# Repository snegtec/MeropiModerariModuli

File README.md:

/*****************************************************************************
*
* MEROPI MODERARI MODULI
* a simple microcontroller system for controlling light output of linear 
* fluorescent tube according to saved program
* 
* version: 0.3 (November 2020)
* author: Erik Kos
*   snegtec.com
*   snegtec@outlook.com
* 
* Copyright (c) 2014-2020 Erik Kos
* License:
*   application, source code - GNU General Public License
*   hardware (schematics, pcb design) - Creative Commons Attribution 
*   Share-Alike license (CC BY-SA 4.0)
* 
****************************************************************************/

Used tools
* compiler: Atmel Studio 6
* application for pcb design: Eagle 6.5.0.

Notes
* this is a beta version!
* pcb for power and relay modules are one-sided; you can create it cheaper than 2 sided versions.

Important note!
* The power module use 230V. There could requirements in your country about design and electrical rules for design of such devices. If you are not confident when working with such voltages don't use the power module. Use ready power supply. 

TODO
* it is better to use external oscilator
* it would be good idea to add socket for serial (txd, rxd); for example during reset Bluetooth connection is lost; it is not a problem in final, production environment but during debug it bothers;
* holes for mounting the boards could have bigger diameter
* cloud events hasn't been tested too carefully; only PWM1 pin has support for cloud events
* no support for daylight saving time 
* add more meaningful captions for elements on pcb boards; like 5V or 3,3V instead of X5 or X3;

Bugs
* There is support for bigger buffer for transmission of AT commands. But sometimes there is a problem that the end of the line disapears when parsed.

Bootloader information
* My version of module uses ATMEL AVR UART Bootloader for AVR-GCC/avr-libc. It is not needed for modules to work. But it can be very helpful to update software when a final module is mounted in a place where there is difficult access.

* MMM software has support for butterfly compatible programmer. It allows for touchless programming of the module. No need to press any button before programming the device. Programmer needs just to use Bluetooth serial port. You start programming, the module resets and bootloader loads into memory and loads new program to memory. More info in utils_com.c file on line 536.

More information about bootloader:
* ATMEL AVR UART Bootloader for AVR-GCC/avr-libc
* by Martin Thomas, Kaiserslautern, Germany
* mthomas@rhrk.uni-kl.de
* eversmith@heizung-thomas.de
* http://www.siwawi.arubi.uni-kl.de/avr_projects

/****************************************************************************/

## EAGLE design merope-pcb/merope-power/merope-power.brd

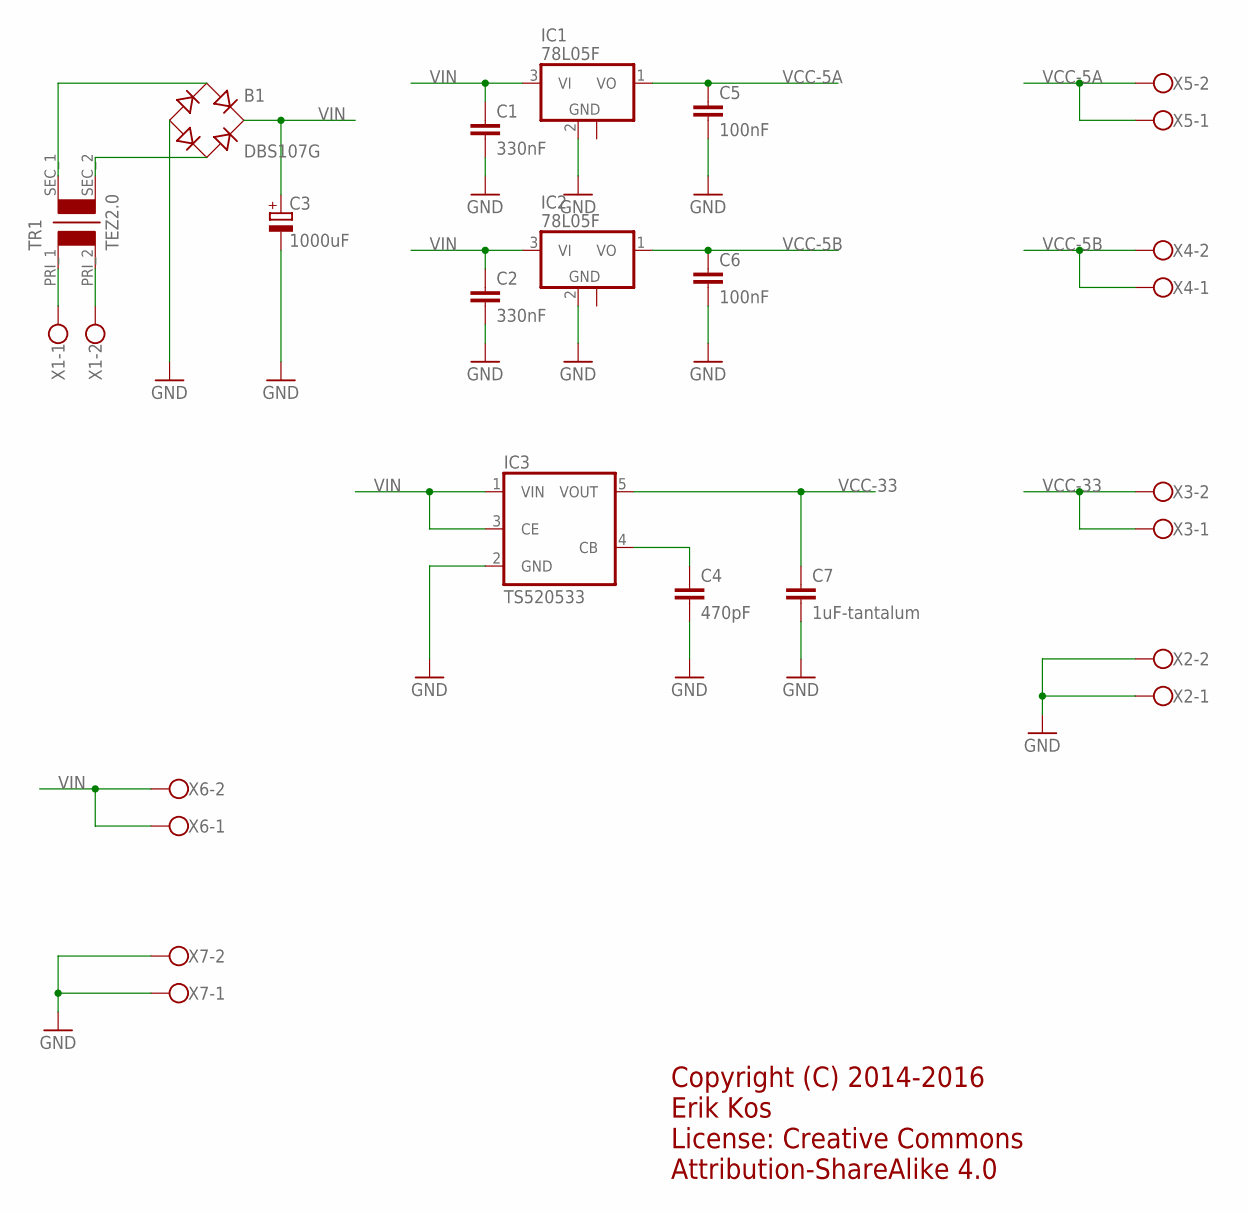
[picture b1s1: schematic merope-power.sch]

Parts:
B1: DBS107G; DBS
C1, C2: 330nF; C0805
C3: 1000uF; TT5D11
C4: 470pF; C0805
C5, C6: 100nF; C0805
C7: 1uF-tantalum; C0805
IC1, IC2: 78L05F; SOT89
IC3: TS520533; SOT25
TR1: TEZ2.0
X1: TERMINAL_BLOCK_5_2
X2, X3, X4, X5, X6, X7: TERMINAL_BLOCK_35_2

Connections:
GND: B1.-, C1.2, C2.2, C3.-, C4.2, C5.2, C6.2, C7.2, IC1.2 (GND), IC2.2 (GND), IC3.2 (GND), X2.1, X2.2, X7.1, X7.2
unnamed: B1.AC1, TR1.SEC_1
unnamed: C4.1, IC3.4 (CB)
unnamed: B1.AC2, TR1.SEC_2
unnamed: TR1.PRI_1, X1.1
unnamed: TR1.PRI_2, X1.2
VCC-5A: C5.1, IC1.1 (VO), X5.1, X5.2
VCC-5B: C6.1, IC2.1 (VO), X4.1, X4.2
VCC-33: C7.1, IC3.5 (VOUT), X3.1, X3.2
VIN: B1.+, C1.1, C2.1, C3.+, IC1.3 (VI), IC2.3 (VI), IC3.1 (VIN), IC3.3 (CE), X6.1, X6.2

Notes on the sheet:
Copyright (C) 2014-2016 Erik Kos License: Creative Commons Attribution-ShareAlike 4.0

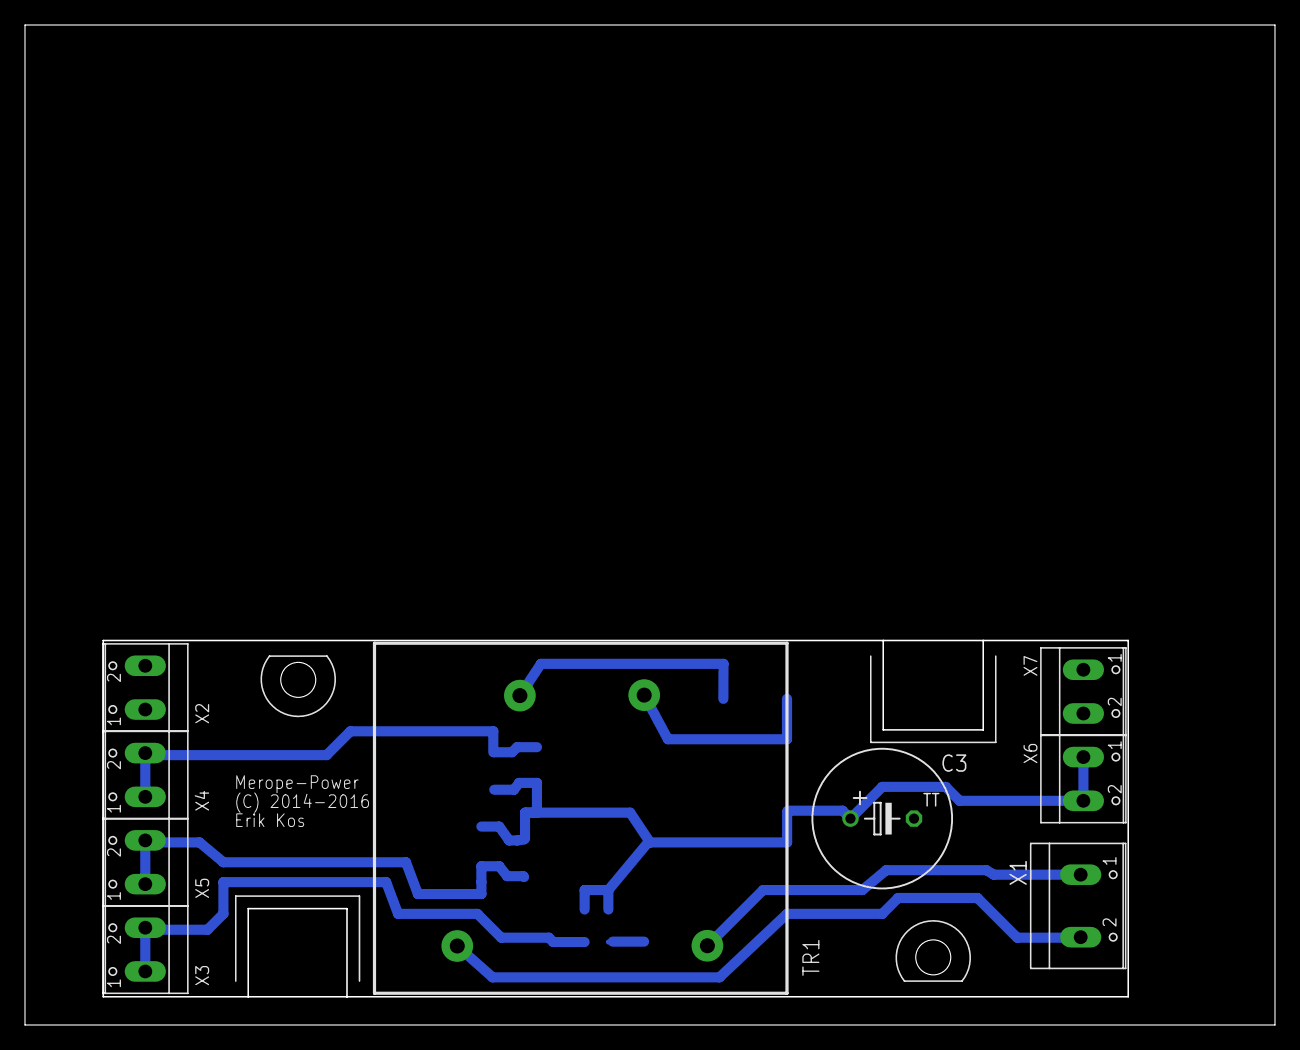
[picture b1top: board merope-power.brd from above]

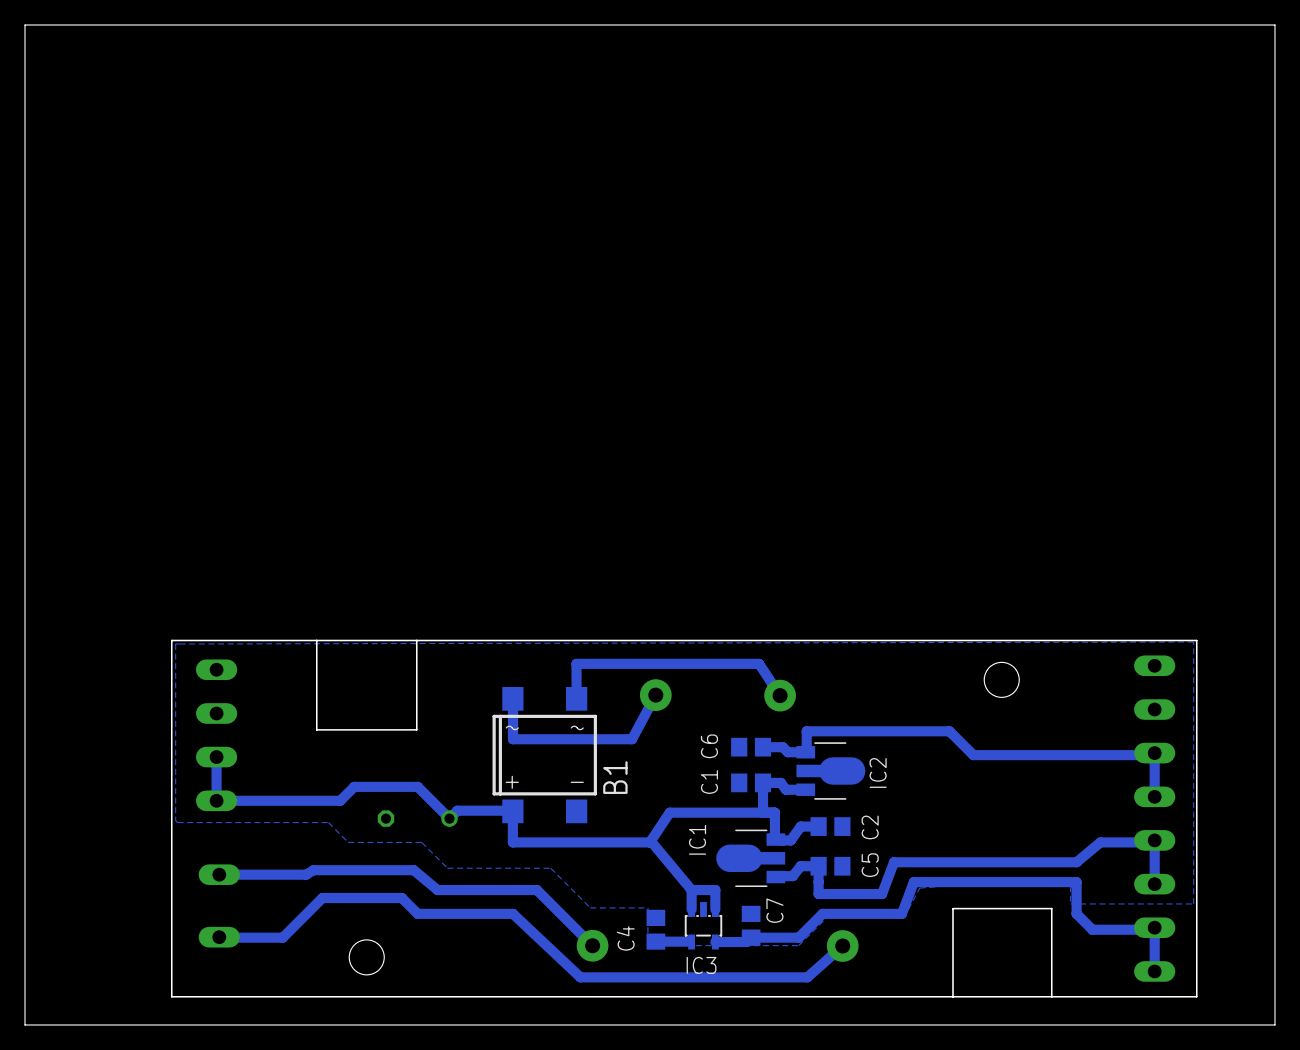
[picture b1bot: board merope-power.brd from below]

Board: 2 copper layers, 100.0 x 80.0 mm, 20 parts (10 on the bottom side), 10 nets.

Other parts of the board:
U$1: Z-103

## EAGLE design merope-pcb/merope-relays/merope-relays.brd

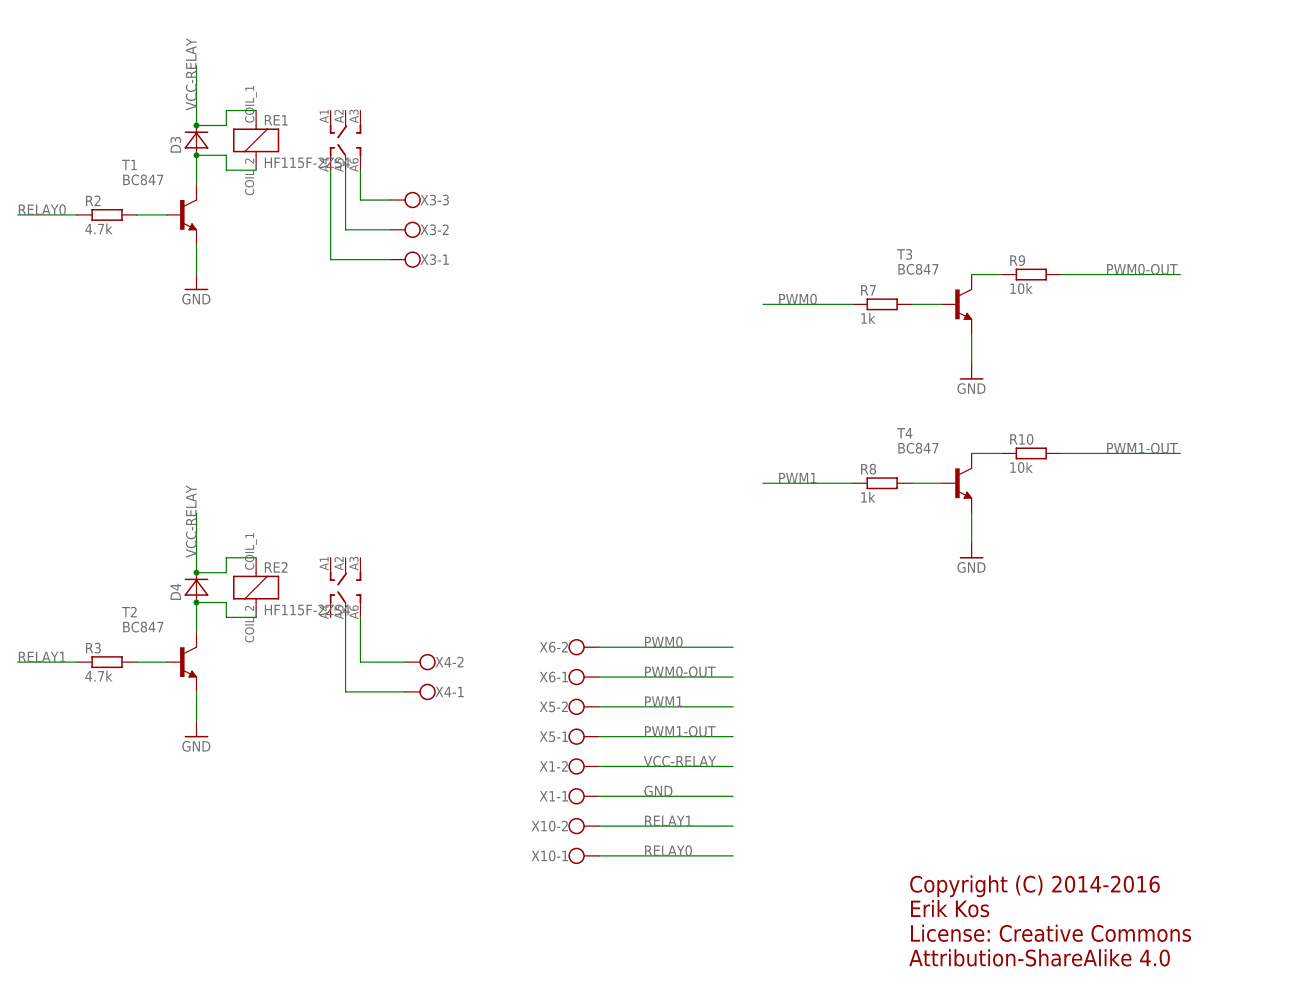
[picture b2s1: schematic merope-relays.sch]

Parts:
D3, D4: DIODE_0805; R0805
R2, R3: 4.7k; M0805
R7, R8: 1k; M0805
R9, R10: 10k; M0805
RE1, RE2: HF115F-2ZS4; HF115F
T1, T2, T3, T4: BC847; SOT23-BEC
X1, X5, X6, X10: TERMINAL_BLOCK_35_2
X3: TERMINAL_BLOCK_5_3
X4: TERMINAL_BLOCK_5_2

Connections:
GND: T1.E, T2.E, T3.E, T4.E, X1.1
unnamed: RE2.A6, X4.2
unnamed: R2.2, T1.B
unnamed: RE1.A6, X3.3
unnamed: RE1.A5, X3.2
unnamed: D3.1 (A), RE1.COIL_2, T1.C
unnamed: RE2.A5, X4.1
unnamed: RE1.A4, X3.1
unnamed: R3.2, T2.B
unnamed: D4.1 (A), RE2.COIL_2, T2.C
unnamed: R7.2, T3.B
unnamed: R9.1, T3.C
unnamed: R8.2, T4.B
unnamed: R10.1, T4.C
PWM0: R7.1, X6.2
PWM0-OUT: R9.2, X6.1
PWM1: R8.1, X5.2
PWM1-OUT: R10.2, X5.1
RELAY0: R2.1, X10.1
RELAY1: R3.1, X10.2
VCC-RELAY: D3.2 (C), D4.2 (C), RE1.COIL_1, RE2.COIL_1, X1.2

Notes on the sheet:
Copyright (C) 2014-2016 Erik Kos License: Creative Commons Attribution-ShareAlike 4.0

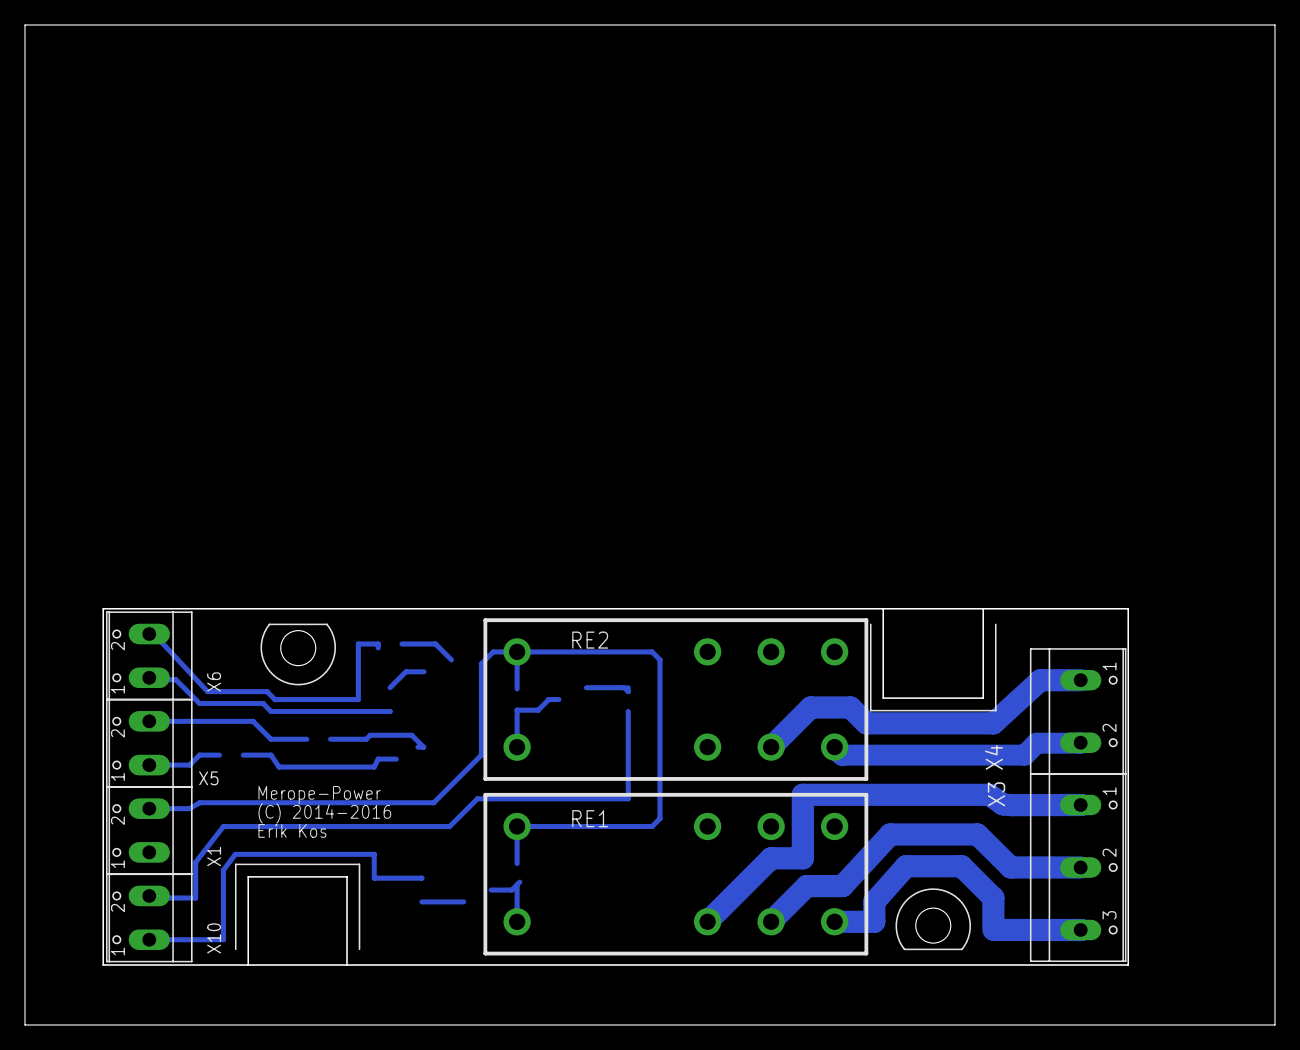
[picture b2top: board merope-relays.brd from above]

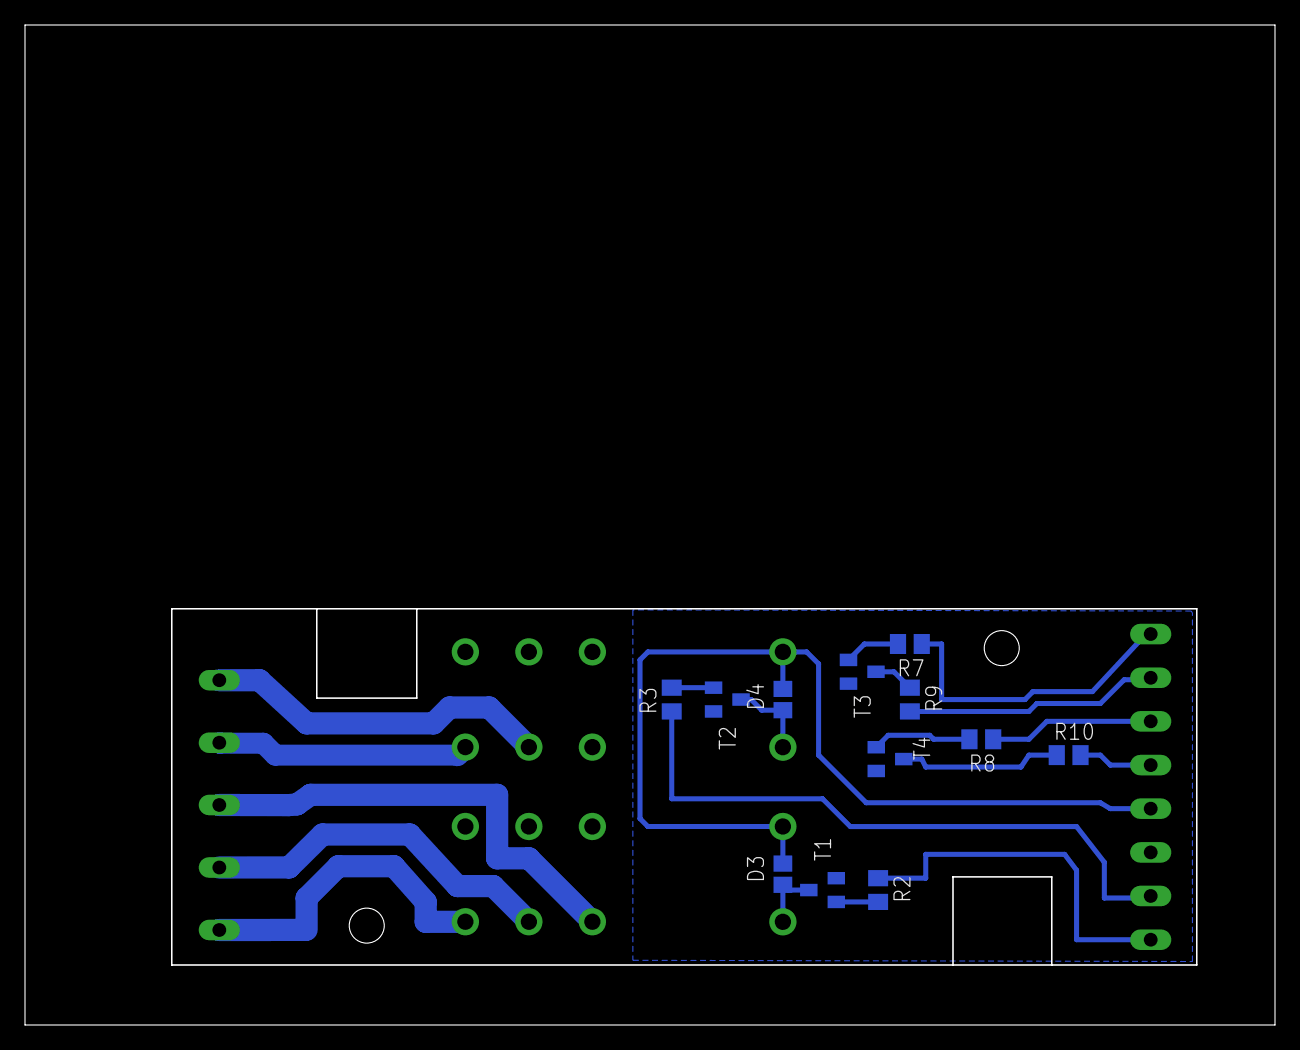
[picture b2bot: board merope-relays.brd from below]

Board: 2 copper layers, 100.0 x 80.0 mm, 21 parts (12 on the bottom side), 21 nets.

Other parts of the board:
U$1: Z-103

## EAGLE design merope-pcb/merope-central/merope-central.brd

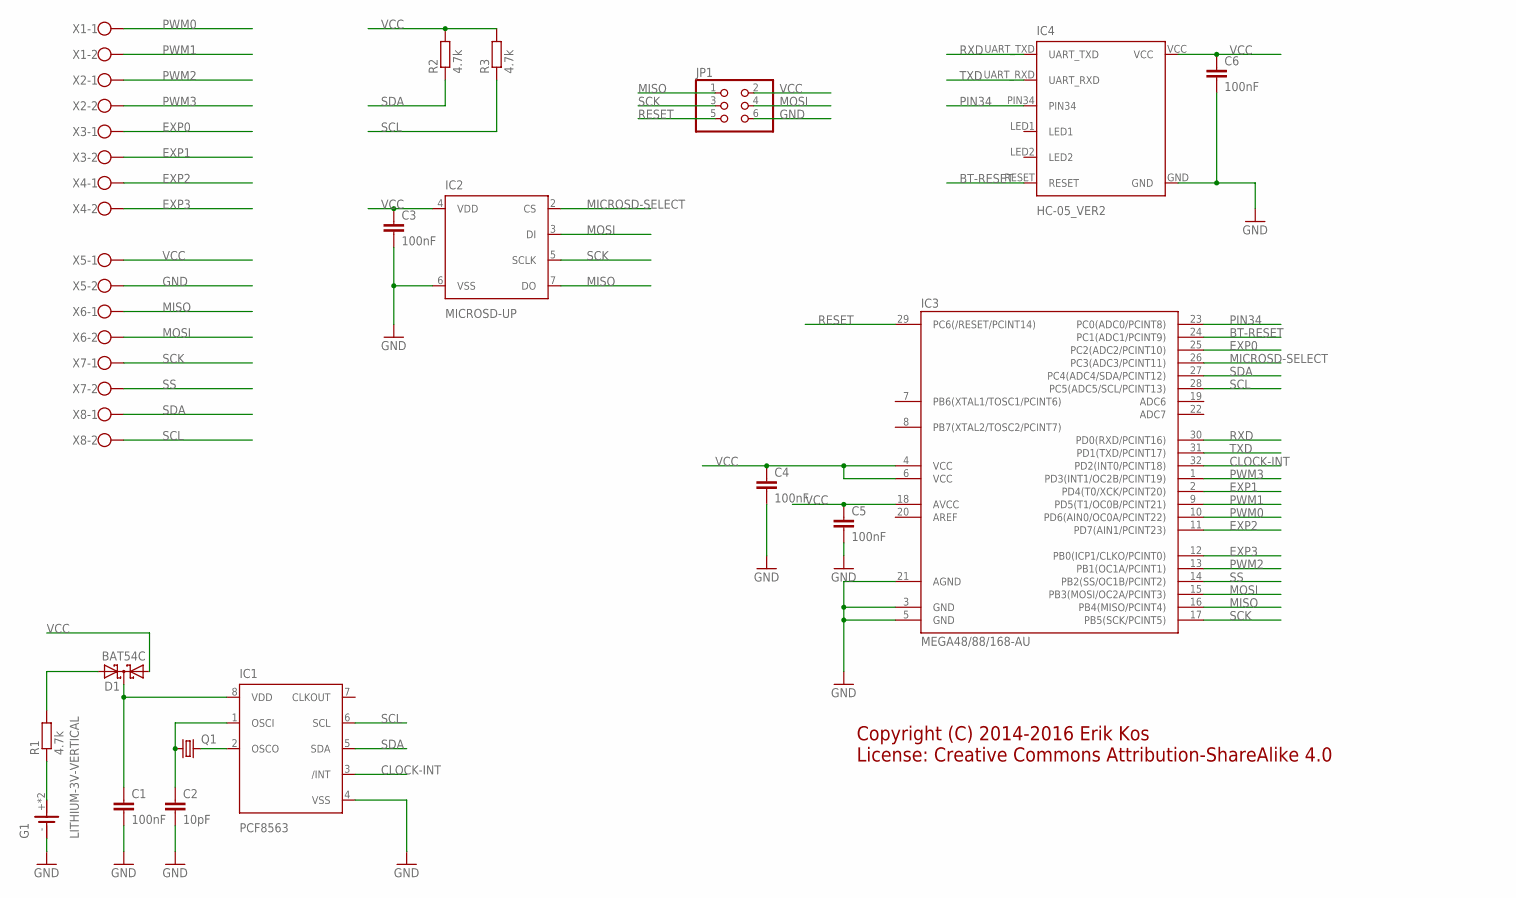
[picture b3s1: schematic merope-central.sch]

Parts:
C1, C3, C4, C5, C6: 100nF; C0805
C2: 10pF; C0805
D1: BAT54C; SOT23
G1: LITHIUM-3V-VERTICAL
IC1: PCF8563; SO8
IC2: MICROSD-UP
IC3: MEGA48/88/168-AU; TQFP32-08
IC4: HC-05_VER2
JP1: PINHD-2X3; 2X03
Q1: CRYSTALTC26V; TC26V
R1, R2, R3: 4.7k; M0805
X1, X2, X3, X4, X5, X6, X7, X8: TERMINAL_BLOCK_35_2

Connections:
BT-RESET: IC3.24 (PC1(ADC1/PCINT9)), IC4.RESET
CLOCK-INT: IC1.3 (/INT), IC3.32 (PD2(INT0/PCINT18))
EXP0: IC3.25 (PC2(ADC2/PCINT10)), X3.1
EXP1: IC3.2 (PD4(T0/XCK/PCINT20)), X3.2
EXP2: IC3.11 (PD7(AIN1/PCINT23)), X4.1
EXP3: IC3.12 (PB0(ICP1/CLKO/PCINT0)), X4.2
GND: C1.2, C2.2, C3.2, C4.2, C5.2, C6.2, G1.-, IC1.4 (VSS), IC2.6 (VSS), IC3.3 (GND), IC3.5 (GND), IC3.21 (AGND), IC4.GND, JP1.6, X5.2
MICROSD-SELECT: IC2.2 (CS), IC3.26 (PC3(ADC3/PCINT11))
MISO: IC2.7 (DO), IC3.16 (PB4(MISO/PCINT4)), JP1.1, X6.1
MOSI: IC2.3 (DI), IC3.15 (PB3(MOSI/OC2A/PCINT3)), JP1.4, X6.2
unnamed: C1.1, D1.3 (CC), IC1.8 (VDD)
unnamed: G1.+, G1.+1 (+), R1.1
unnamed: D1.2 (A2), R1.2
unnamed: IC1.2 (OSCO), Q1.2
unnamed: C2.1, IC1.1 (OSCI), Q1.1
PIN34: IC3.23 (PC0(ADC0/PCINT8)), IC4.PIN34
PWM0: IC3.10 (PD6(AIN0/OC0A/PCINT22)), X1.1
PWM1: IC3.9 (PD5(T1/OC0B/PCINT21)), X1.2
PWM2: IC3.13 (PB1(OC1A/PCINT1)), X2.1
PWM3: IC3.1 (PD3(INT1/OC2B/PCINT19)), X2.2
RESET: IC3.29 (PC6(/RESET/PCINT14)), JP1.5
RXD: IC3.30 (PD0(RXD/PCINT16)), IC4.UART_TXD
SCK: IC2.5 (SCLK), IC3.17 (PB5(SCK/PCINT5)), JP1.3, X7.1
SCL: IC1.6 (SCL), IC3.28 (PC5(ADC5/SCL/PCINT13)), R3.1, X8.2
SDA: IC1.5 (SDA), IC3.27 (PC4(ADC4/SDA/PCINT12)), R2.1, X8.1
SS: IC3.14 (PB2(SS/OC1B/PCINT2)), X7.2
TXD: IC3.31 (PD1(TXD/PCINT17)), IC4.UART_RXD
VCC: C3.1, C4.1, C5.1, C6.1, D1.1 (A1), IC2.4 (VDD), IC3.4 (VCC), IC3.6 (VCC), IC3.18 (AVCC), IC4.VCC, JP1.2, R2.2, R3.2, X5.1

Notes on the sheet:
Copyright (C) 2014-2016 Erik Kos License: Creative Commons Attribution-ShareAlike 4.0

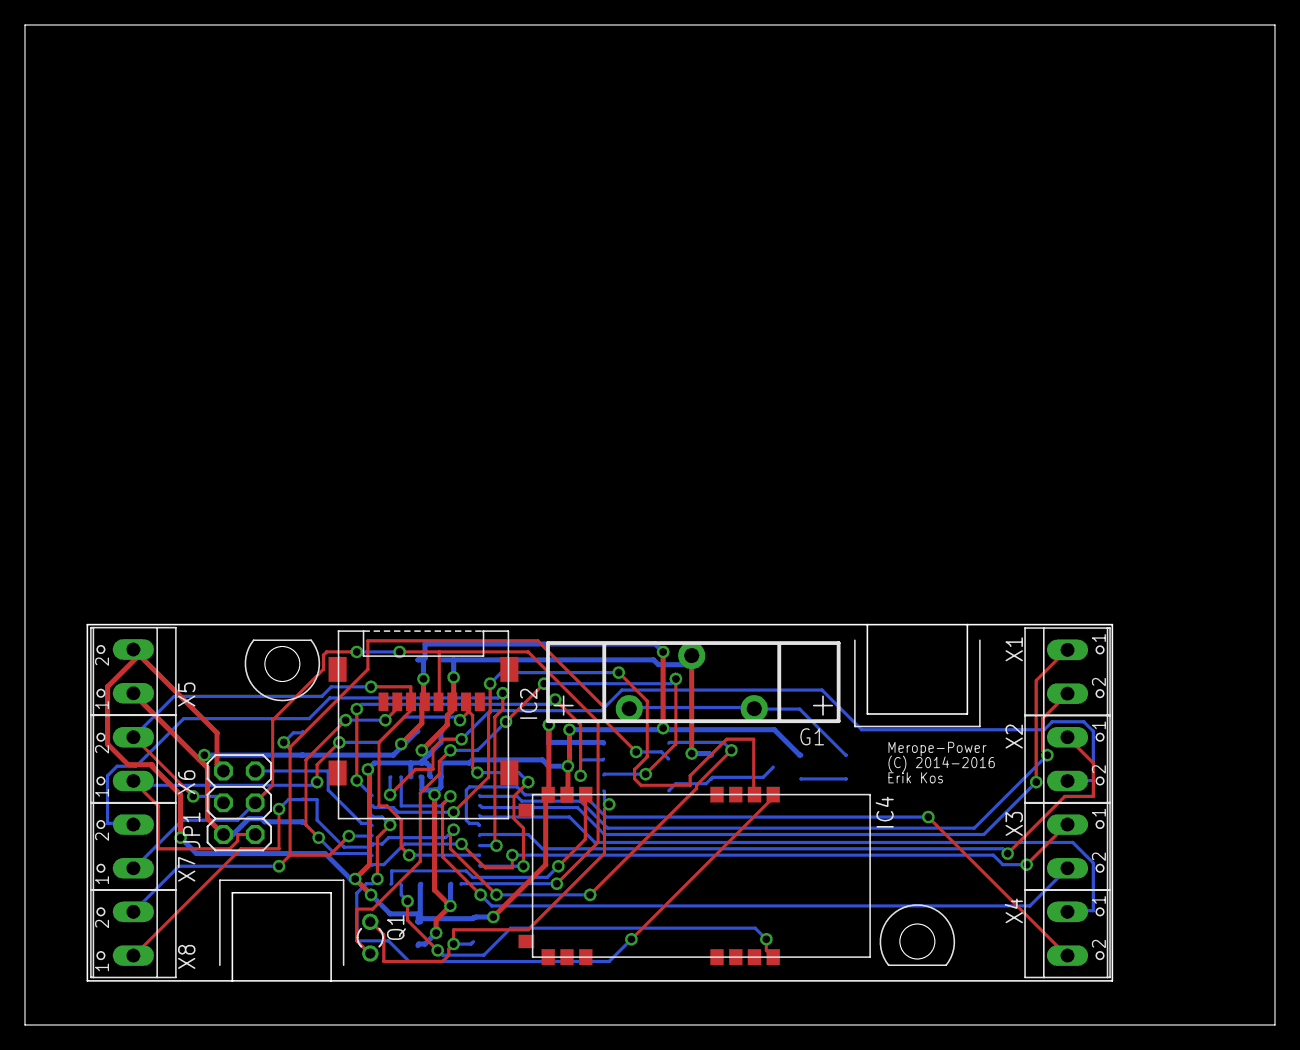
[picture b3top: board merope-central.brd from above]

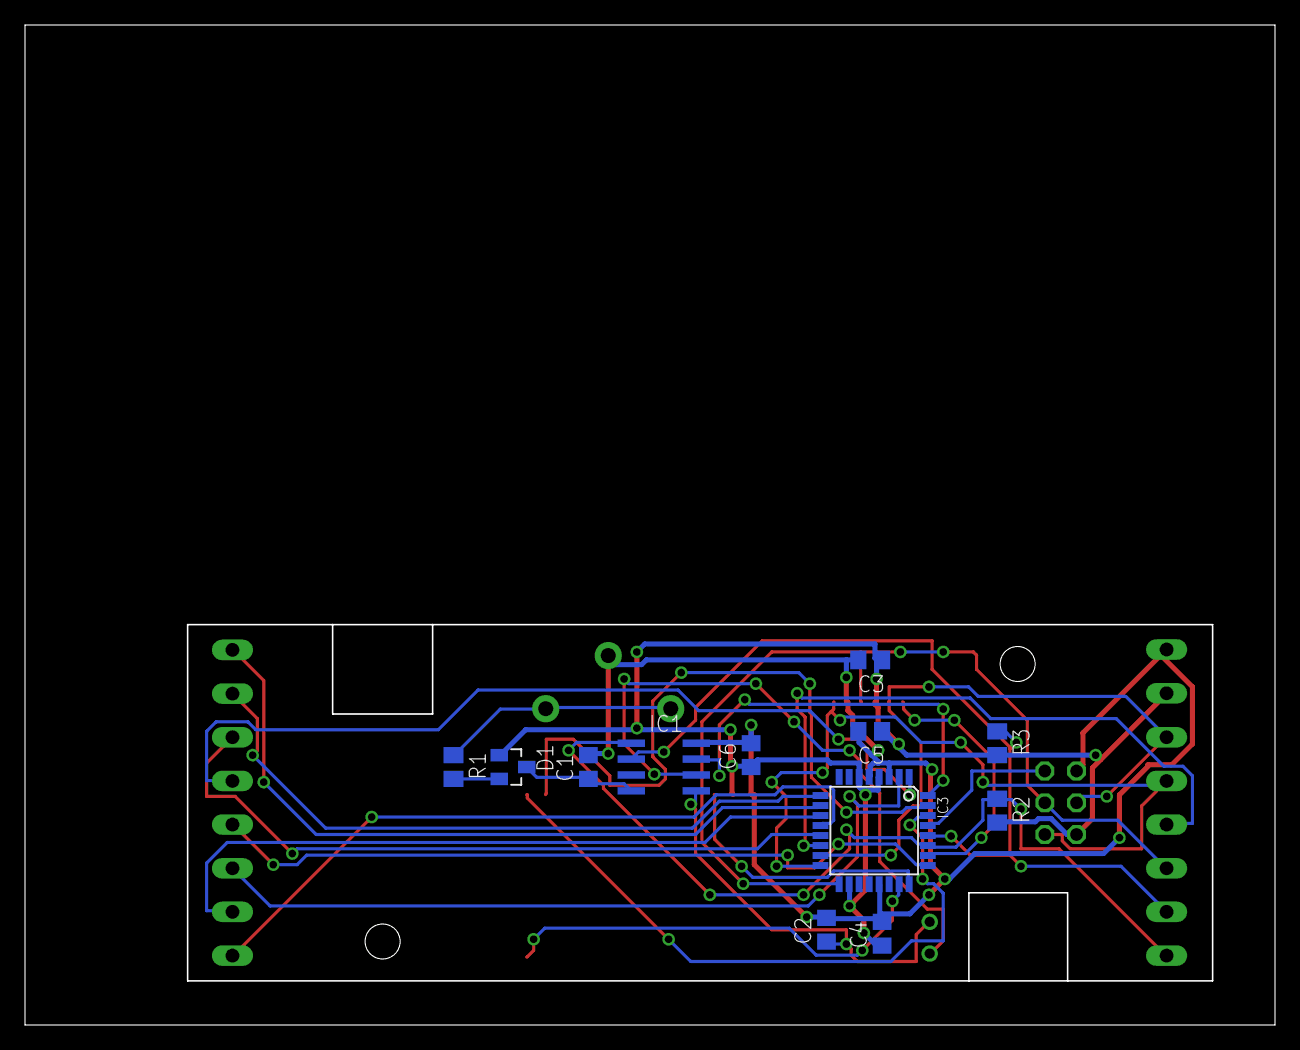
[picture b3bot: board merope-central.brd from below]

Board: 2 copper layers, 100.0 x 80.0 mm, 26 parts (12 on the bottom side), 28 nets.

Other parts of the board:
U$1: Z-103

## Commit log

2016-05-11 full content
    full content - first public version
2017-12-05 20171205
    Some small bug fixes
2017-12-05 20171205a
    Readme file change
2020-11-14 Added some files and changed some information.
